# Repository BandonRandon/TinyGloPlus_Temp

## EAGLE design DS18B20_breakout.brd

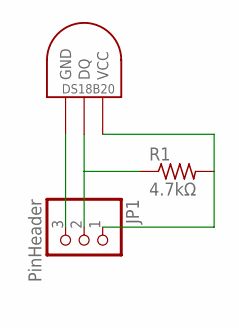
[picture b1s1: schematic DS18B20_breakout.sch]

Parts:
JP1: PinHeader; 1X03
R1: 4.7kΩ; 0207/7
U$1: DS1820TO92; DS1820

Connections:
unnamed: JP1.3, U$1.GND
unnamed: JP1.2, R1.1, U$1.DQ
unnamed: JP1.1, R1.2, U$1.VDD (VCC)

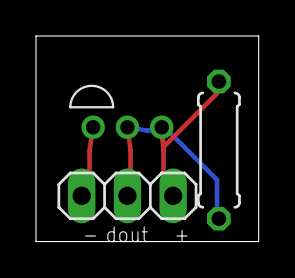
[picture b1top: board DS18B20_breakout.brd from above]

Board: 2 copper layers, 12.4 x 11.4 mm, 3 parts (0 on the bottom side), 3 nets.

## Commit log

2016-03-27 Add Files
